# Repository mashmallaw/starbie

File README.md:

# starbie
small tamagotchi life creature that lives with you

Hi ! I'm alex and this is how i made my starby : 
first i started with the schematic on kicad following the tutorial

then I put it though the pcb editor and routed it, adding small drawings and such

Finally, I made the firmware with Arduino, adding things such as a sparkle effect and a personalized sprite.

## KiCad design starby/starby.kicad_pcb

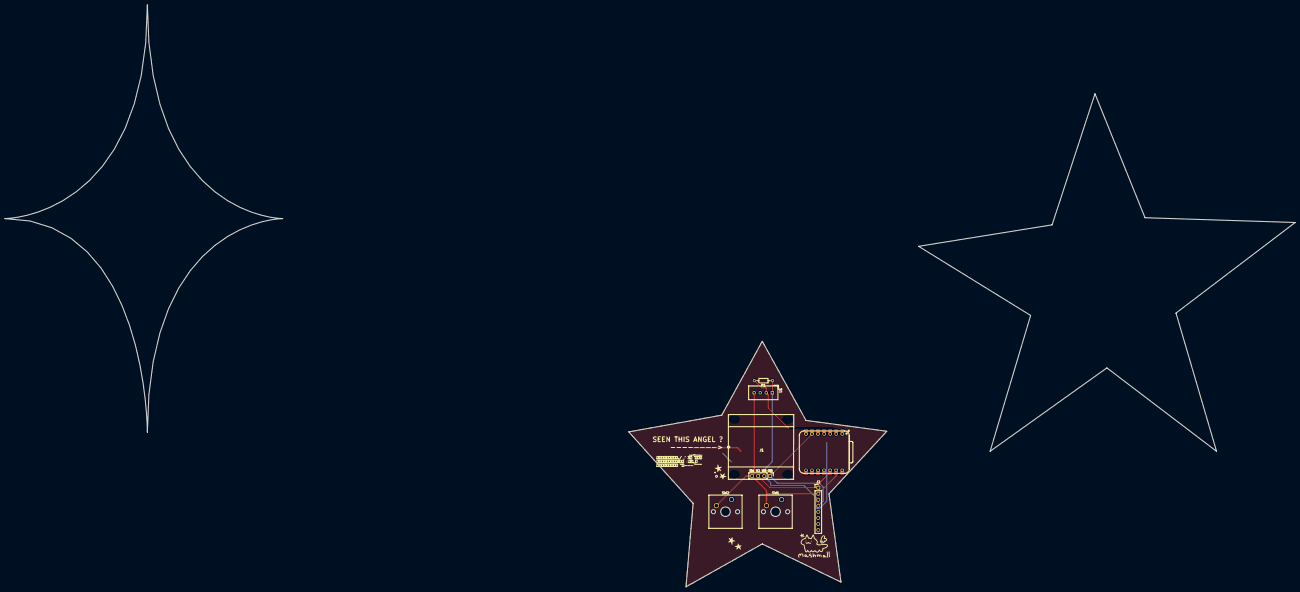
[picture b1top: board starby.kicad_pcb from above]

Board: 2 copper layers, 108.2 x 103.0 mm, 7 parts (0 on the bottom side), 5 nets.

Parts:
J1: Conn_01x04_Pin; Display_128x64_096_I2C
J2: Conn_01x08_Pin; PinHeader_1x08_P2.54mm_Vertical
R1: 10K; R_Axial_DIN0204_L3.6mm_D1.6mm_P7.62mm_Horizontal
SW1, SW2: SW_Push; SW_Cherry_MX_1.00u_PCB
U1: DHT11; Aosong_DHT11_5.5x12.0_P2.54mm
U2: XIAO-ESP32-C3-SMD; XIAO-ESP32-C6-DIP

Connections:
+3.3V: J1.3, J2.1, R1.1, U1.1 (VDD), U2.12 (3V3_OUT)
/DHT11 DATA: R1.2, U1.2 (DATA), U2.2 (D1)
/SCL: J1.2, J2.3, U2.5 (D4)
/SDA: J1.1, J2.4, U2.6 (D5)
GND: J1.4, J2.2, SW1.2, SW2.2, U1.4 (GND), U2.13 (GND)
